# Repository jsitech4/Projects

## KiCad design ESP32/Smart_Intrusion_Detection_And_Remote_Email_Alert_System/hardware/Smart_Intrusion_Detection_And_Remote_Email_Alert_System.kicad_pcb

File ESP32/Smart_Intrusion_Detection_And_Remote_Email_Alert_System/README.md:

# Smart Intrusion Detection and Remote Email Alert System

Standalone ESP32 intrusion detector with local audible alarm, Gmail SMTPS notification, secure local administration, and first-time Wi-Fi provisioning. It reuses the original ESP32 PCB mappings and contains no ESP-NOW or mesh operation.

## Verified PCB mapping

| Function           |  GPIO | Notes                                                        |
| ------------------ | ----: | ------------------------------------------------------------ |
| PIR input          |    26 | HIGH is treated as motion; GPIO26 is RTC-capable.            |
| Buzzer             |    23 | Original firmware energised it HIGH.                         |
| Status LED         |     2 | Active-HIGH patterned status, alert, fault, and network LED. |
| Test button        |    27 | Original active-LOW PCB button, with external bias assumed.  |
| Battery ADC        |    34 | Input-only, original divider scale 1.61.                     |
| Battery gauge LEDs | 16–19 | Active-HIGH 25%, 50%, 75%, and 100% battery-level bars.      |

## Operation

After the configured PIR warm-up, a HIGH PIR signal stable for the motion-confirmation period opens an intrusion event. The buzzer starts immediately, an email is queued on a separate FreeRTOS task, and the current alarm window runs without blocking sensing or the web server. At every alarm boundary, confirmed motion continues the same event and starts another cycle; confirmed clear state ends it.

The device retains only the most recent eight completed intrusion events. This rolling history automatically overwrites the oldest event, keeping persistent storage use predictable and avoiding unnecessary flash growth.

## LED indicators

GPIO2 is the single status LED. Its patterns have priority in this order: intrusion, critical battery, low battery, system fault, Wi-Fi loss, internet loss, PIR warm-up, and configuration mode.

| GPIO2 pattern          | Meaning                                           |
| ---------------------- | ------------------------------------------------- |
| Three rapid flashes    | Intrusion alarm is active.                        |
| Four short flashes     | Critical battery.                                 |
| Two medium flashes     | Low battery.                                      |
| Two fault flashes      | A persistent firmware/system fault.               |
| One long flash         | Wi-Fi is disconnected.                            |
| Two very short flashes | Wi-Fi is connected but the internet check failed. |
| One brief heartbeat    | Powered, healthy, and internet-reachable.         |

GPIO16, GPIO17, GPIO18, and GPIO19 form a cumulative battery bar: one, two, three, or four LEDs represent 1–25%, 26–50%, 51–75%, and 76–100% respectively. The gauge is off when battery monitoring is disabled or the estimated level is empty. Internet reachability is checked with a short TCP probe every 30 seconds; it confirms an external route, not every online service.

## Reliability and automated checks

The ESP32 loop task is protected by a 10-second task watchdog. It is fed only after the complete control loop has run, so a stalled loop resets the device instead of leaving it unresponsive. A reset caused by the watchdog is retained as a fault indication after restart.

The native scenario suite covers battery-gauge boundaries, status-LED priority and pulse timing, and both repeat-alarm paths. Run `tools\run_scenario_tests.bat` to execute it automatically with installed Visual Studio C++ Build Tools. On machines using GCC or MinGW, `platformio test -e native` also works. The production firmware build remains `platformio run -e esp32dev`.

The physical button has two distinct behaviours:

- A short press simulates a PIR intrusion using the complete alarm, log, and notification path.
- Holding it for five seconds opens the configuration access point for two minutes after initial setup. A long press does not simulate an intrusion.

During a configuration window, join the `IntrusionDetector-XXXX` AP. Its generated WPA2 password and `192.168.4.1` address are printed on the serial monitor. On a first boot without saved Wi-Fi, the AP remains active until Wi-Fi is configured.

## Local dashboard and security

Open the device IP address or `http://intrusion-detector.local` after connection. The first visitor must choose an administrator password of at least 12 characters; it is stored as a salted SHA-256 hash. API calls use a time-limited RAM session and CSRF token. Wi-Fi and Gmail passwords are never returned by the configuration API.

This is local HTTP, not HTTPS. Use it only on a trusted LAN and set a strong administrator password. The AP password is emitted only to serial output; treat that serial connection as privileged.

## Gmail

Enter the sender Gmail address, a Google App Password, one to five recipient addresses, and an alert message in the dashboard. Put multiple addresses in the **Recipient email** field separated with commas, semicolons, or line breaks. Addresses are checked, duplicates are removed, and each message uses private SMTP envelope recipients so recipients do not see one another. The firmware connects to `smtp.gmail.com:465` by default and validates TLS with the Google Trust Services root. An accepted SMTP submission is not proof of inbox delivery.

The email subject is generated as `SECURITY ALERT - <device name>`. The alert message is sent exactly as written, followed automatically by the device location, event ID, and NTP-synchronized Nigeria time. The occurrence timestamp is captured when the intrusion begins, so a delayed delivery still reports the original event time.

## Time in Nigeria

The default timezone is `WAT-1` (West Africa Time, UTC+1), which is the POSIX timezone string for Nigeria. After Wi-Fi connects, the ESP32 synchronizes with multiple NTP servers and keeps local event timestamps and email times in WAT. If the connection is lost, it derives time from the last trusted NTP reading and elapsed ESP32 uptime until NTP is available again. The dashboard displays the device's synchronized time; until its first successful NTP sync it reports that the time is unavailable. Keep the timezone set to `WAT-1` for operation in Nigeria.

## Battery-divider calibration

The battery divider scale converts the ESP32 ADC reading on GPIO34 into the actual battery voltage:

```text
battery voltage = ADC-pin voltage × battery divider scale
```

The default scale is `1.61`, taken from the original PCB. To calibrate it, measure the battery with a multimeter (`Vbattery`) and compare it with the voltage shown in the dashboard (`Vshown`). Then save:

```text
new divider scale = current divider scale × (Vbattery ÷ Vshown)
```

For example, if the current scale is `1.61`, the multimeter reads `4.00 V`, and the dashboard reports `3.80 V`, use `1.61 × (4.00 ÷ 3.80) = 1.695`. Recheck the displayed value after saving; calibrate at a normal battery operating voltage.

## Build and flash

Install PlatformIO, then run from this folder:

```powershell
& "$env:USERPROFILE\.platformio\penv\Scripts\platformio.exe" run
& "$env:USERPROFILE\.platformio\penv\Scripts\platformio.exe" run --target upload
& "$env:USERPROFILE\.platformio\penv\Scripts\platformio.exe" device monitor --baud 115200
```

The current target is `esp32dev` (ESP32-WROOM-class, 4 MB flash). Firmware output is `.pio/build/esp32dev/firmware.bin`.

## UI preview

Open [preview_UI/test.html](preview_UI/test.html) in a browser for a static preview of the dashboard. It is illustrative only; it does not connect to an ESP32.

## Commissioning checklist

1. Verify PIR output voltage never exceeds 3.3 V and is LOW while idle.
2. Confirm GPIO23 buzzer polarity and the GPIO2 LED polarity on the physical PCB.
3. Confirm a short button press triggers one alarm cycle and a five-second hold opens AP mode without an alarm.
4. Configure Wi-Fi, Gmail App Password, and up to five recipients; use **Send test email** and confirm delivery to each inbox.
5. Test PIR HIGH for 20, 45, and 65 seconds, then test clear before and at an alarm boundary.
6. Measure sleep/idle power before enabling a battery-saver deep-sleep mode; PIR module, LED, regulator, and ADC divider currents are board-specific and must be measured.

## Security and local configuration

Never commit populated `.env` files, Wi-Fi credentials, passwords, API keys, SMTP credentials, broker tokens, private certificates, or production connection strings. Keep them in an ignored local configuration file or approved secret store, and commit only a redacted `.env.example` when configuration is needed. Replace development access-point credentials before deployment and limit local administration to trusted networks.

# Author

Egbe Raymond

Electrical / Electronic Engineer
Embedded Systems Developer
Full Stack Developer

---

## Engineering asset map and license scope

The editable electrical package is under `hardware/` as a KiCad project,
schematic, and PCB, with project library/3D materials. `documentation/`
contains the schematic and block diagrams, ESP32 reference, and board images;
`production/` contains the BOM, Gerbers, positions, designators, and IPC
netlist. Inspect and modify the source project, then regenerate manufacturing
outputs for a replacement board.

The PlatformIO/Arduino code in `code/` targets `esp32dev` at 115200 baud and
also declares a native test environment. Its modules separate PIR/button
input, buzzer/LED state, Wi-Fi and email delivery, intrusion policy and
controller, event logging/configuration, web administration, battery handling,
and error management. SMTP credentials, Wi-Fi credentials, recipient data, and
event records are deployment secrets or personal data and must not be committed.

The asset-type table below covers original firmware, KiCad files, original images/exports, and project
documentation. ESP32 and sensor material, third-party libraries, mail-service
terms, vendor assets, and trademarks are not relicensed. Consult the
[license scope guide](../../LICENSE-SCOPE.md) and do not treat this prototype
as a certified life-safety or security-response system.

## Licenses

The original JSI Tech material in this mixed engineering project is licensed by
asset type:

| Material | License | Scope |
| --- | --- | --- |
| Software and firmware | [MIT](LICENSE) | Original source code, scripts, configuration examples, tests, and web assets in `code/`. |
| Hardware design | [CERN-OHL-P-2.0](LICENSE-HARDWARE) | Original KiCad/design and manufacturing material in `hardware/` and `production/`. |
| Documentation | [CC BY 4.0](LICENSE-DOCUMENTATION) | Original README text, written documentation, diagrams, photos, and screenshots. |
| External material | [Third-party notices](THIRD-PARTY-NOTICES.md) | Vendor data, third-party libraries/models, dependencies, logos, and other material not created by JSI Tech. |

The [collection licensing guide](../../LICENSE-SCOPE.md) explains the boundary,
required notices, and limitations.

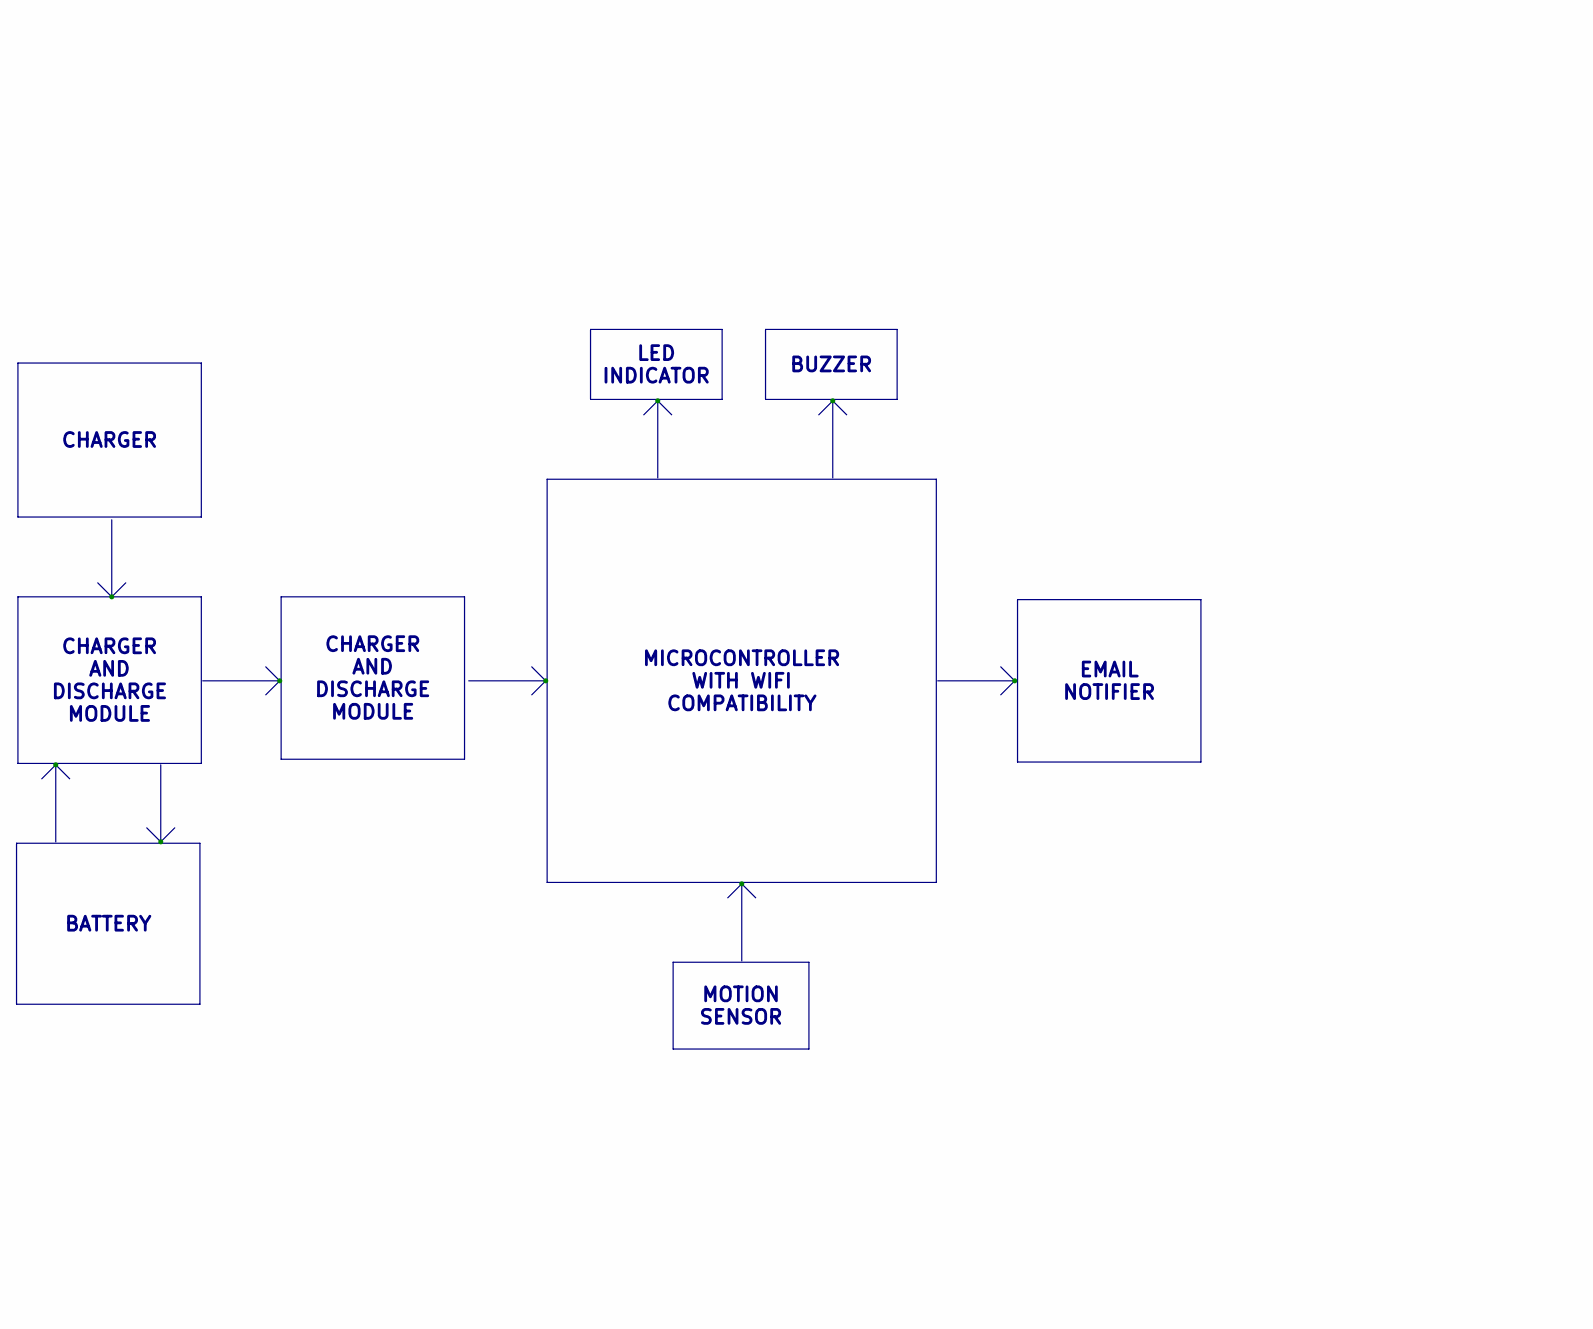
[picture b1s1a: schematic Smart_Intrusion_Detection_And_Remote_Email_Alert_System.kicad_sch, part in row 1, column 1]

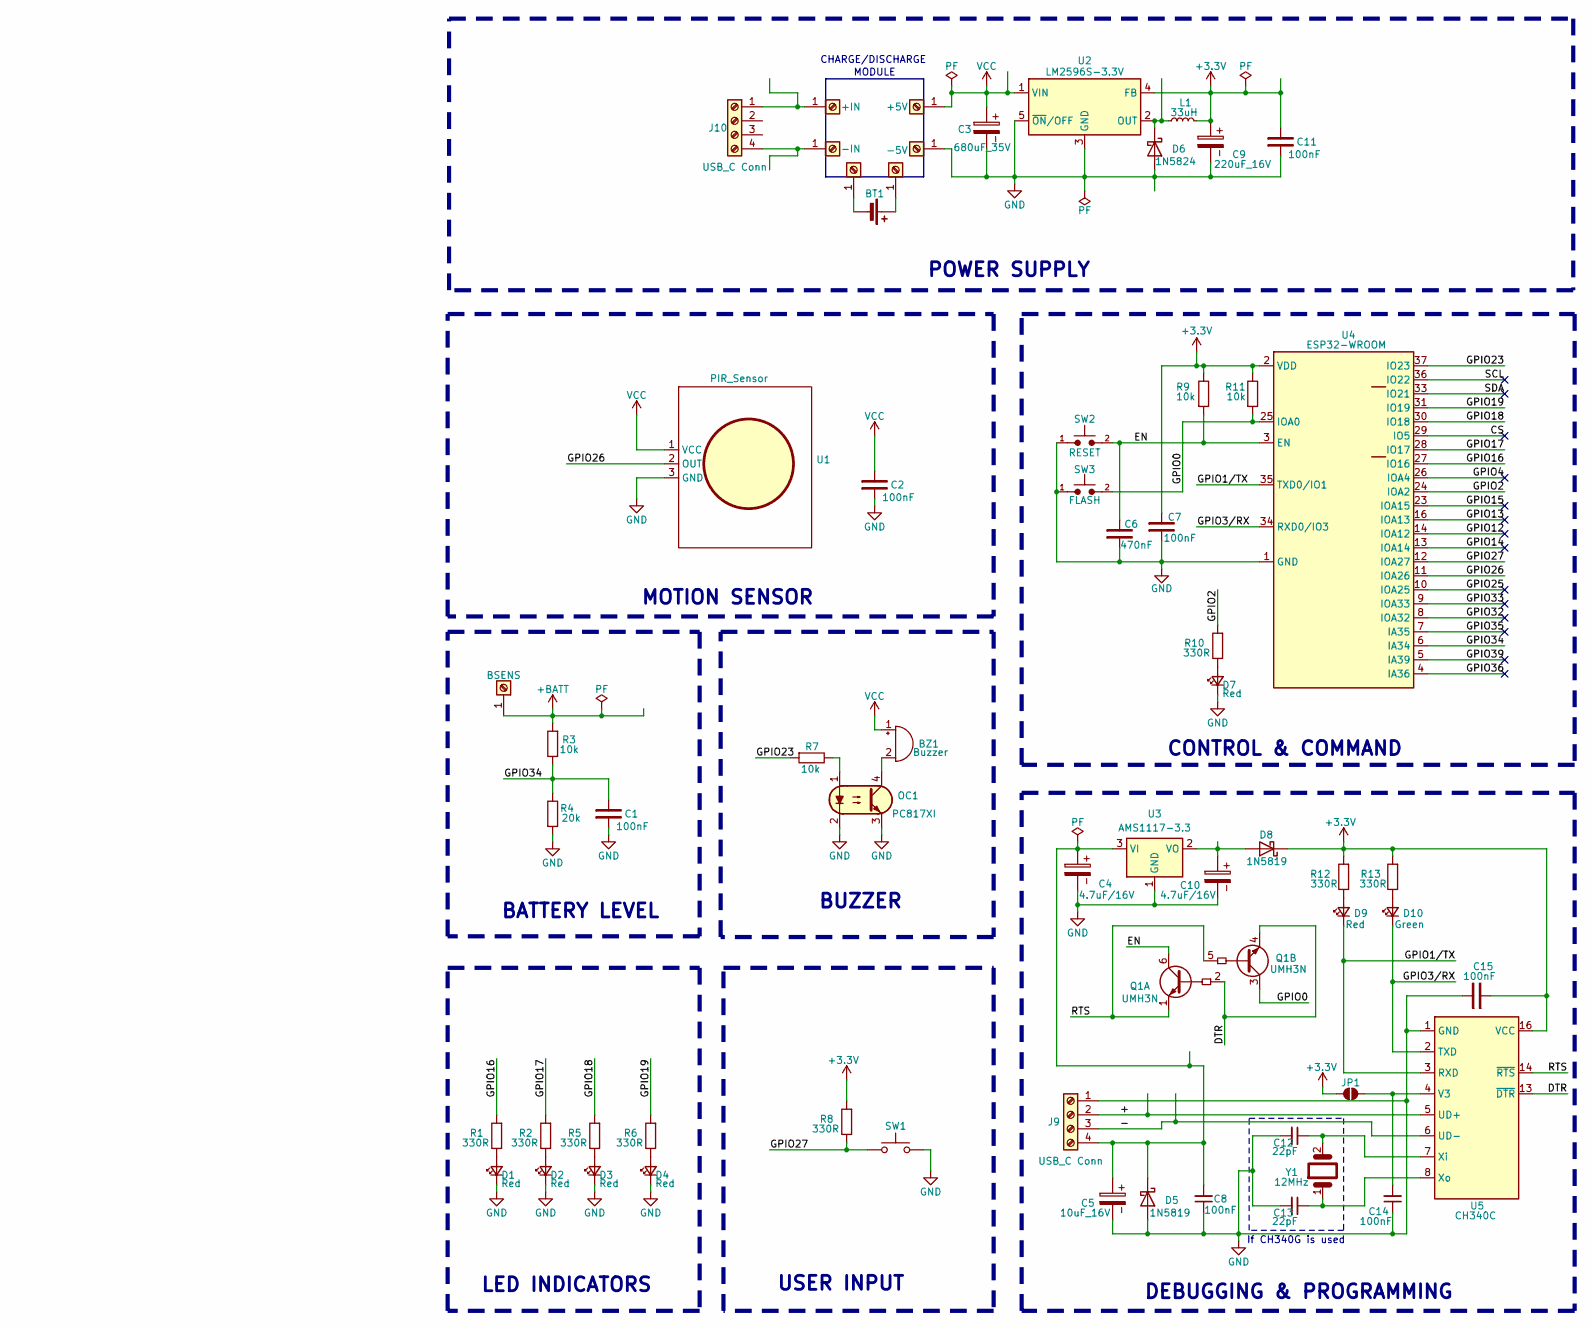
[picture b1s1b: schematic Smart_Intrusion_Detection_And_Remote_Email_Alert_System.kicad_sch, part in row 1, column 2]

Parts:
BT1: Battery_Cell
BZ1: Buzzer; Buzzer_15x7.5RM7.6
C1, C2, C7, C8, C11, C14, C15: 100nF; C_0805_2012Metric_Pad1.18x1.45mm_HandSolder
C3: 680uF_35V; CP_Elec_10x12.5
C4, C10: 4.7uF/16V; CP_EIA-3528-21_Kemet-B_HandSolder
C5: 10uF_16V; CP_Radial_D5.0mm_P2.00mm
C6: 470nF; C_0805_2012Metric_Pad1.18x1.45mm_HandSolder
C9: 220uF_16V; CP_Elec_6.3x7.7
C12, C13: 22pF; C_0805_2012Metric_Pad1.18x1.45mm_HandSolder
D1, D2, D3, D4, D7, D9: Red; LED_D3.0mm
D5, D8: 1N5819; D_SMA
D6: 1N5824; D_SMA
D10: Green; LED_D3.0mm
J1: BSENS; SolderWire-0.1sqmm_1x01_D0.4mm_OD1mm
J3: +IN; TestPoint_Keystone_5015_Micro_Mini
J4: -IN; TestPoint_Keystone_5015_Micro_Mini
J5: -BATT
J6: +BATT
J7: +5V; TestPoint_Keystone_5015_Micro_Mini
J8: -5V; TestPoint_Keystone_5015_Micro_Mini
J9, J10: USB_C Conn; PinHeader_1x04_P2.54mm_Vertical
JP1: SolderJumper-2_P1.3mm_Open_Pad1.0x1.5mm
L1: 33uH; L_12x12mm_H6mm
OC1: PC817XI; SMDIP-4_W9.53mm
Q1: UMH3N; SOT-363_SC-70-6
R1, R2, R5, R6, R8, R10, R12, R13: 330R; R_0805_2012Metric
R3, R7, R9, R11: 10k; R_0805_2012Metric
R4: 20k; R_0805_2012Metric
SW1: SW_Push; PinHeader_1x02_P2.54mm_Vertical
SW2: RESET; SW_SPST_CK_KXT3
SW3: FLASH; SW_SPST_CK_KXT3
U1: PIR_Sensor; PinHeader_1x03_P2.54mm_Vertical
U2: LM2596S-3.3V; TO-263-5_TabPin6
U3: AMS1117-3.3; SOT-223-3_TabPin2
U4: ESP32-WROOM; ESP32-WROOM-32U
U5: CH340C; SOIC-16_3.9x9.9mm_P1.27mm
Y1: 12MHz; Crystal_HC49-4H_Vertical

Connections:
+3.3V: C7.2, C9.1, C11.2, C15.1, D8.1 (K), JP1.2 (B), L1.2, R8.1, R9.2, R11.2, R12.1, R13.1, U2.4 (FB), U4.2 (VDD), U5.16 (VCC)
+BATT: J1.1, R3.1
/+: J9.2, U5.5 (UD+)
/-: J9.3, U5.6 (UD-)
/CS: U4.29 (IO5)
/DTR: Q1.2 (B1), Q1.4 (E2), U5.13 (~DTR)
/EN: C6.2, Q1.6 (C1), R9.1, SW2.2, U4.3 (EN)
/GPIO0: Q1.3 (C2), R11.1, SW3.2, U4.25 (IOA0)
/GPIO1/TX: D9.1 (K), U4.35 (TXD0/IO1), U5.3 (RXD)
/GPIO2: R10.1, U4.24 (IOA2)
/GPIO3/RX: D10.1 (K), U4.34 (RXD0/IO3), U5.2 (TXD)
/GPIO4: U4.26 (IOA4)
/GPIO12: U4.14 (IOA12)
/GPIO13: U4.16 (IOA13)
/GPIO14: U4.13 (IOA14)
/GPIO15: U4.23 (IOA15)
/GPIO16: R1.1, U4.27 (IO16)
/GPIO17: R2.1, U4.28 (IO17)
/GPIO18: R5.1, U4.30 (IO18)
/GPIO19: R6.1, U4.31 (IO19)
/GPIO23: R7.1, U4.37 (IO23)
/GPIO25: U4.10 (IOA25)
/GPIO26: U1.2 (OUT), U4.11 (IOA26)
/GPIO27: R8.2, SW1.1, U4.12 (IOA27)
/GPIO32: U4.8 (IOA32)
/GPIO33: U4.9 (IOA33)
/GPIO34: C1.2, R3.2, R4.2, U4.6 (IA34)
/GPIO35: U4.7 (IA35)
/GPIO36: U4.4 (IA36)
/GPIO39: U4.5 (IA39)
/RTS: Q1.1 (E1), Q1.5 (B2), U5.14 (~RTS)
/SCL: U4.36 (IO22)
/SDA: U4.33 (IO21)
GND: C1.1, C2.1, C3.2, C4.2, C5.2, C6.1, C7.1, C8.1, C9.2, C10.2, C11.1, C12.2, C13.2, C14.1, C15.2, D1.1 (K), D2.1 (K), D3.1 (K), D4.1 (K), D5.2 (A), D6.2 (A), D7.1 (K), J8.1, J9.1, OC1.2, OC1.3, R4.1, SW1.2, SW2.1, SW3.1, U1.3 (GND), U2.3 (GND), U2.5 (~ON/OFF), U2.6 (GND), U3.1 (GND), U4.1 (GND), U4.15 (GND), U4.38 (GND), U4.39 (GND), U5.1 (GND)
unnamed: BT1.1 (+), J6.1
unnamed: BT1.2 (-), J5.1
unnamed: BZ1.2 (-), OC1.4
unnamed: D1.2 (A), R1.2
unnamed: D2.2 (A), R2.2
unnamed: D3.2 (A), R5.2
unnamed: D4.2 (A), R6.2
unnamed: C4.1, C5.1, C8.2, D5.1 (K), J9.4, U3.3 (VI)
unnamed: D6.1 (K), L1.1, U2.2 (OUT)
unnamed: D7.2 (A), R10.2
unnamed: C10.1, D8.2 (A), U3.2 (VO)
unnamed: D9.2 (A), R12.2
unnamed: D10.2 (A), R13.2
unnamed: J3.1, J10.1
unnamed: J4.1, J10.4
unnamed: C14.2, JP1.1 (A), U5.4 (V3)
unnamed: OC1.1, R7.2
unnamed: C12.1, U5.7 (Xi), Y1.2
unnamed: C13.1, U5.8 (Xo), Y1.1
VCC: BZ1.1 (+), C2.2, C3.1, J7.1, U1.1 (VCC), U2.1 (VIN)

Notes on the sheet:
MOTION SENSOR
MODULE
BUZZER
POWER SUPPLY
CHARGE/DISCHARGE
If CH340G is used
BATTERY LEVEL
LED INDICATORS
DEBUGGING & PROGRAMMING
CONTROL & COMMAND
USER INPUT
MOTION SENSOR
LED INDICATOR
CHARGER
EMAIL NOTIFIER
BATTERY
MICROCONTROLLER WITH WIFI COMPATIBILITY
CHARGER AND DISCHARGE MODULE

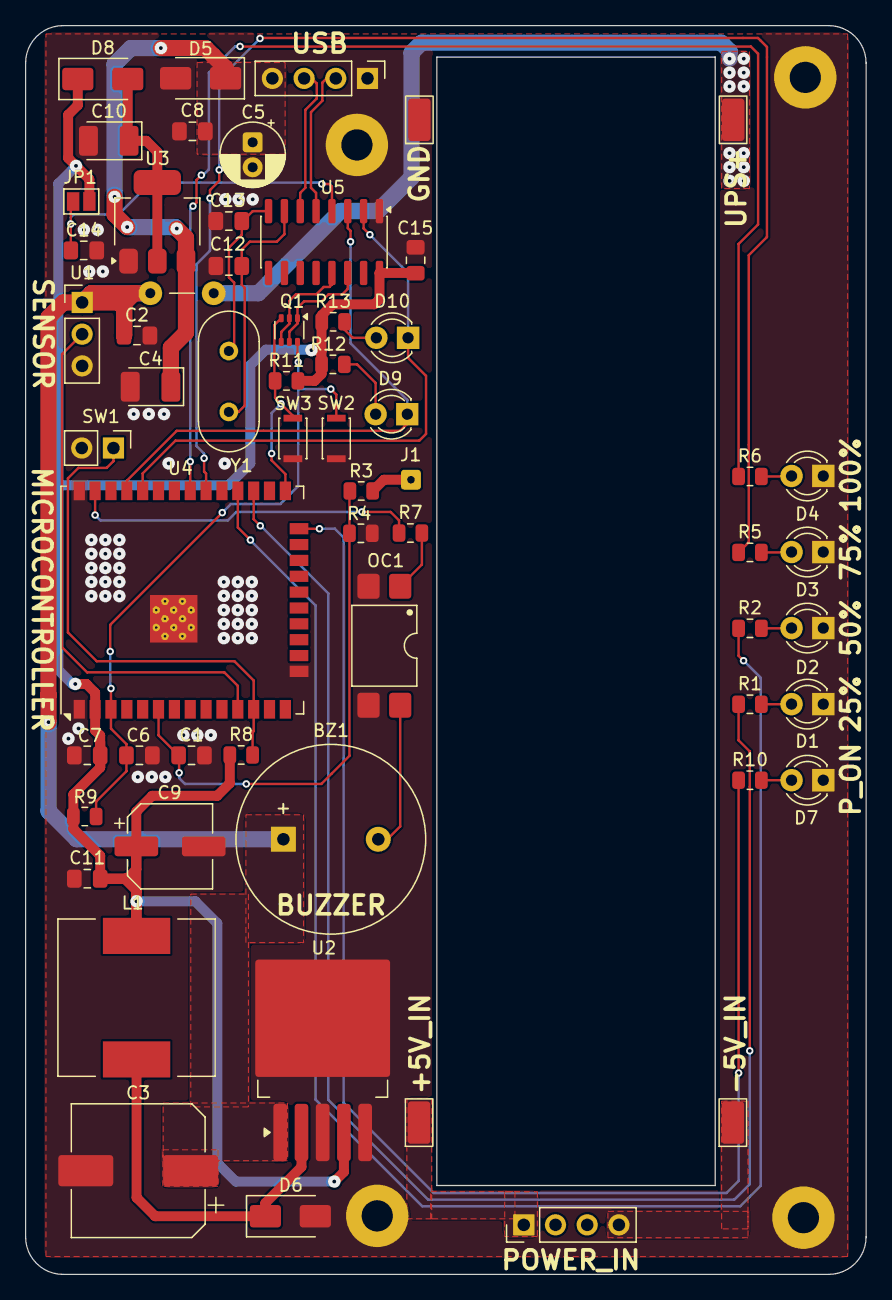
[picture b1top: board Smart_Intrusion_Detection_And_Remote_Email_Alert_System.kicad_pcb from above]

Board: 2 copper layers, 67.3 x 100.0 mm, 59 parts (0 on the bottom side), 38 nets.

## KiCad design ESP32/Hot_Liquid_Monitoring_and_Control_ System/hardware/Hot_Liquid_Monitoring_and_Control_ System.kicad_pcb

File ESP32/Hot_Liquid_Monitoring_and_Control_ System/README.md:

# Hot Liquid Monitoring and Control System

ESP32-S3 firmware and KiCad hardware for monitoring liquid temperature and vessel level, presenting live status on a local dashboard/LCD, recording events, and driving a protected relay output according to configurable level and temperature rules.

## What it does

- Measures temperature through a MAX31865 RTD interface and liquid distance/level through an ultrasonic sensor.
- Converts distance to a configurable percentage level and classifies low/normal/full tank states.
- Classifies temperature against configurable low/high limits.
- Combines independent automatic demands with a persistent manual relay request; the effective relay request is `manual OR automatic`.
- Provides latching modes for tank and temperature events, a buzzer/LED indication path, local web dashboard, LCD output, internal flash settings/event storage, sleep/wake service, and reset handling.

## Hardware mapping

| Function | ESP32-S3 GPIO | Notes |
| --- | ---: | --- |
| I2C SDA / SCL | 8 / 9 | LCD and I2C peripherals. |
| ZMCT103C ADC | 1 | Defined on the PCB pin map; verify use before enabling. |
| ADXL345 interrupt | 10 | Defined on the PCB pin map; not part of the primary control loop. |
| DS18B20 data | 4 | Defined on the PCB pin map. |
| SPI CS / MOSI / SCK / MISO | 5 / 11 / 12 / 13 | Reserved interface pins. |
| Ultrasonic trigger / echo | 17 / 18 | Level sensor; condition echo voltage for 3.3 V logic. |
| Buzzer | 14 | Active level must match the installed driver. |
| Relay | 21 | Verify relay polarity and load isolation before use. |
| Status LED | 48 | Local state indication. |
| UART0 TX / RX | 43 / 44 | Serial/programming interface. |
| Boot | 0 | Do not load in a way that prevents boot. |

The deployed hardware and source of truth are in `hardware/` and `code/lib/Pins/Pins.cpp`. Review the KiCad schematic before connecting sensors or mains-powered equipment.

## Operating model

At startup the firmware restores a validated saved configuration or retains safe defaults. Each loop updates the RTD and ultrasonic sensors, evaluates `device_manager`, applies the relay request, updates buzzer/LED/LCD/storage/web services, and yields. A latched automatic threshold event cannot be cleared merely by changing settings: `clearFault()` rechecks valid, current inputs and clears only when all enabled threshold conditions have recovered. Manual relay requests remain separate from faults.

The local web UI exposes live state, configuration, event records, manual relay control, and guarded fault clearing. Treat browser controls as an operator interface—not as a substitute for thermal cut-outs, pressure relief, contactors, or independent safety interlocks.

## Build, upload, and test

Prerequisites: PlatformIO Core, an ESP32-S3 DevKitC-1, and the components stated in `platformio.ini` (LiquidCrystal_I2C, Adafruit ADXL345, and Adafruit MAX31865).

```powershell
cd code
pio run -e esp32-s3
pio device list
pio run -e esp32-s3 -t upload
pio device monitor -b 115200
```

Run the host fault tests from `code` using the project’s test configuration. Before energizing a live actuator, test with the relay load disconnected, verify the output polarity, calibrate full/low vessel distances, validate temperature limits with a reference thermometer, and confirm the relay remains de-energized on reset and sensor error.

## Configuration and usage

1. Wire only isolated, low-voltage sensor signals. The ultrasonic echo input must be reduced to 3.3 V logic.
2. Flash the firmware and connect to the device’s local access point/dashboard as reported by the firmware.
3. Set full and low distances, level thresholds, temperature limits, and the intended latch modes.
4. Verify level conversion with known vessel levels; verify the RTD reading against a trusted thermometer.
5. Test automatic demand, manual demand, latch clearing, buzzer/LED, dashboard, and persistence with no hazardous load attached.
6. Connect the final relay through a correctly rated, isolated driver and independently verify fail-safe behavior.

## Project layout

| Path | Purpose |
| --- | --- |
| `hardware/` | KiCad project, symbols, footprints, 3D models, and PCB design. |
| `code/src/` | Firmware entry point and initialization order. |
| `code/lib/Control/` | Control state, fault logic, sleep/reset, and device manager. |
| `code/lib/Sensors/` | RTD and ultrasonic acquisition. |
| `code/lib/Actuators/`, `Display/`, `Communication/` | Relay, buzzer, UI, and local server. |
| `code/lib/Storage/` | Persistent settings and event history. |
| `production/` | BOM, fabrication, and Gerber deliverables. |

## Security and secrets

Do not place Wi-Fi credentials, local dashboard passwords, cloud/API tokens, or private certificates in committed source. Store them in a local `.env`/ignored configuration file and inject them during the build or provisioning process; provide only a redacted `.env.example` when adding configuration. Change any development access-point password before deployment, restrict the configuration network to trusted users, and do not expose an unauthenticated control UI to the internet.

## Safety

Hot liquid, heaters, pumps, and mains equipment can cause burns, fire, electrocution, or pressure hazards. This project is not a certified safety controller. Use a qualified electrician, fused and grounded hardware, rated contactors/SSR drivers, a mechanical thermal cut-out, independent over-temperature and dry-run protection, emergency isolation, and local regulatory requirements. Never rely on firmware alone to protect people or equipment.

# Author

Egbe Raymond

Electrical / Electronic Engineer
Embedded Systems Developer
Full Stack Developer

---

## Engineering asset map and license scope

The KiCad schematic, PCB, and project source are in `hardware/`; its symbols,
footprints, 3D assets, source imagery, block/schematic PDFs, and ESP32-S3
reference are kept with `hardware/` and `documentation/`. `production/`
contains Gerbers, BOM, positions, designators, and IPC netlist for fabrication.
Review the schematic and regenerate these exports after any electrical change.

`code/` is an Arduino PlatformIO firmware project for `esp32-s3-devkitc-1` at
115200 baud. Modules isolate temperature and ultrasonic sensing, relay and
buzzer actuation, LCD/LED indication, storage, local web service, device
management, error handling, reset, and sleep/wake behavior. The firmware is a
prototype control implementation; set points, sensor calibration, relay
polarity, fail-safe state, and over-temperature protection must be verified on
the actual vessel and load.

The asset-type table below applies to original project firmware, KiCad sources, original library
assets, fabrication exports, images, and documentation. Datasheets, vendor
models, external libraries, components, and tool output governed by another
notice are excluded from that grant. See the [license scope guide](../../LICENSE-SCOPE.md),
especially its hardware and safety section.

## Licenses

The original JSI Tech material in this mixed engineering project is licensed by
asset type:

| Material | License | Scope |
| --- | --- | --- |
| Software and firmware | [MIT](LICENSE) | Original source code, scripts, configuration examples, tests, and web assets in `code/`. |
| Hardware design | [CERN-OHL-P-2.0](LICENSE-HARDWARE) | Original KiCad/design and manufacturing material in `hardware/` and `production/`. |
| Documentation | [CC BY 4.0](LICENSE-DOCUMENTATION) | Original README text, written documentation, diagrams, photos, and screenshots. |
| External material | [Third-party notices](THIRD-PARTY-NOTICES.md) | Vendor data, third-party libraries/models, dependencies, logos, and other material not created by JSI Tech. |

The [collection licensing guide](../../LICENSE-SCOPE.md) explains the boundary,
required notices, and limitations.

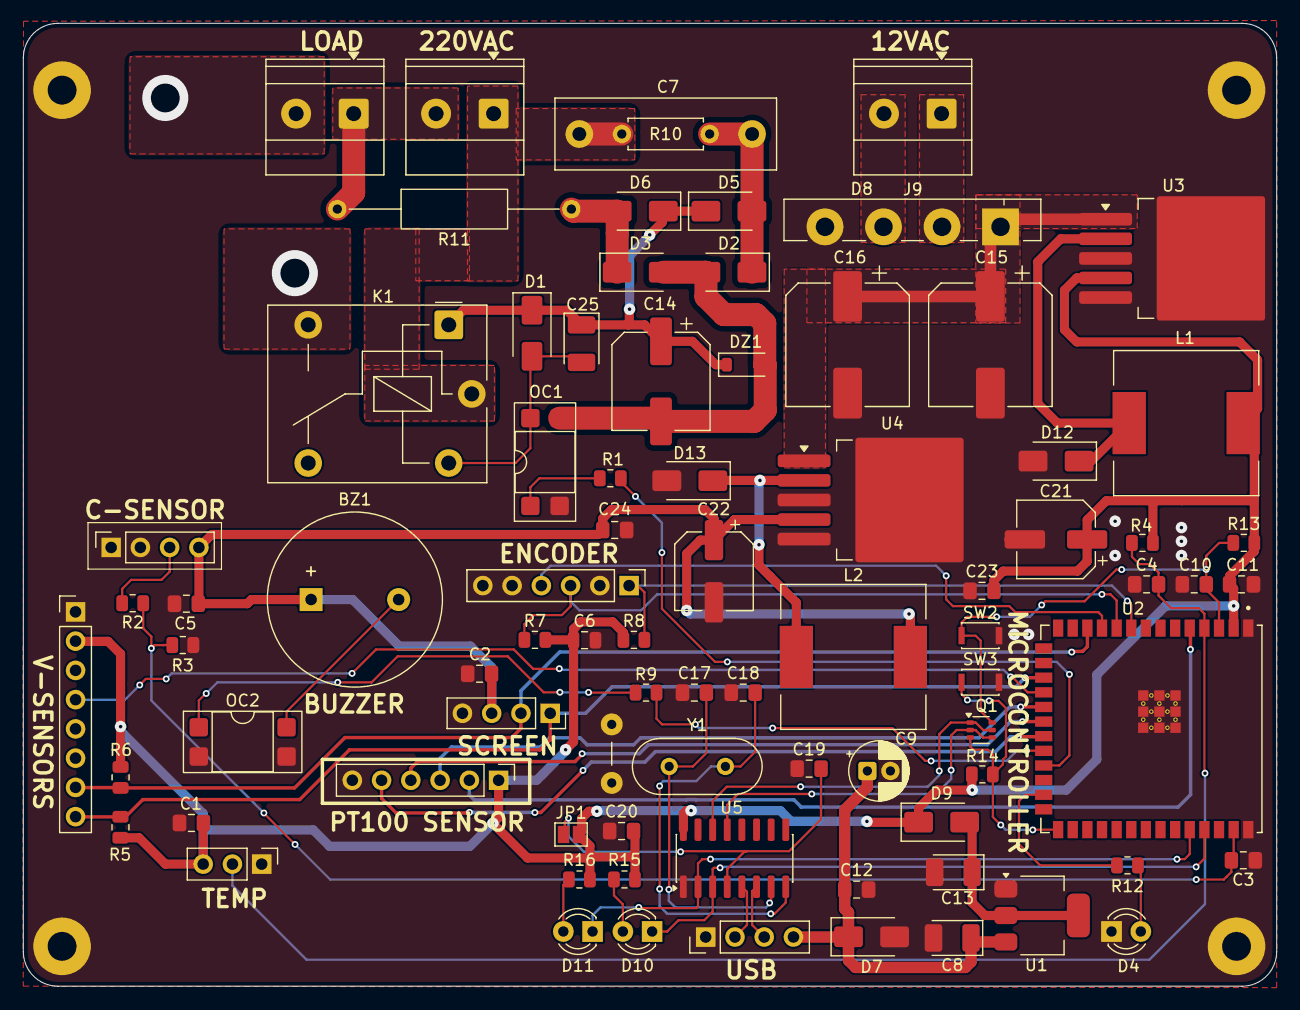
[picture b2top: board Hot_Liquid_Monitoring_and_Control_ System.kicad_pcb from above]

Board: 2 copper layers, 108.8 x 83.6 mm, 81 parts (0 on the bottom side), 51 nets.

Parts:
BZ1: Buzzer; Buzzer_15x7.5RM7.6
C1, C2, C3, C4, C5, C11, C12, C19, C20, C23, C24: 100nF; C_0805_2012Metric_Pad1.18x1.45mm_HandSolder
C6: 104; C_0805_2012Metric
C7: 145J400V; C_Rect_L19.0mm_W6.0mm_P15.00mm_MKS4
C8, C13, C25: 4.7uF/16V; CP_EIA-3528-21_Kemet-B_HandSolder
C9: 10uF_16V; CP_Radial_D5.0mm_P2.00mm
C10: 470nF; C_0805_2012Metric_Pad1.18x1.45mm_HandSolder
C14: 470uF/25V; CP_Elec_8x11.9
C15, C16: 680uF_35V; CP_Elec_10x12.5
C17, C18: 22pF; C_0805_2012Metric_Pad1.18x1.45mm_HandSolder
C21, C22: 220uF_16V; CP_Elec_6.3x7.7
D1: 1N4007; D_SMA
D2, D3, D5, D6: SM4001; D_SMA
D4, D10: Red; LED_D3.0mm
D7, D9: 1N5819; D_SMA
D8: GBU8M; Diode_Bridge_Vishay_GBU
D11: Green; LED_D3.0mm
D12, D13: 1N5824; D_SMA
DZ1: CMZ12; D_SOD-123
J1: DS18B20; PinHeader_1x03_P2.54mm_Vertical
J2: CURRENT SENSOR; PinSocket_1x04_P2.54mm_Vertical
J3: OLED SCREEN; PinSocket_1x04_P2.54mm_Vertical
J4: LOAD; TerminalBlock_Phoenix_MKDS-1,5-2_1x02_P5.00mm_Horizontal
J5: 220VAC; TerminalBlock_Phoenix_MKDS-1,5-2_1x02_P5.00mm_Horizontal
J6: MPU6050; PinHeader_1x08_P2.54mm_Vertical
J7: SD MODULE; PinHeader_1x06_P2.54mm_Vertical
J8: USB_C Conn; PinHeader_1x04_P2.54mm_Vertical
J9: 12VAC; TerminalBlock_Phoenix_MKDS-1,5-2_1x02_P5.00mm_Horizontal
JP1: SolderJumper-2_P1.3mm_Open_Pad1.0x1.5mm
K1: FINDER-36.11; Relay_SPDT_Finder_36.11
L1, L2: 33uH; L_12x12mm_H6mm
OC1, OC2: PC817XI; DIP-4_W7.62mm_SMDSocket_SmallPads
Q1: UMH3N; SOT-363_SC-70-6
R1, R4, R5, R6, R7, R8, R9, R13, R14: 10k; R_0805_2012Metric
R2: 1k; R_0805_2012Metric
R3: 2k; R_0805_2012Metric
R10: 1M; R_Axial_DIN0207_L6.3mm_D2.5mm_P7.62mm_Horizontal
R11: 330R/2W; R_Axial_DIN0309_L9.0mm_D3.2mm_P20.32mm_Horizontal
R12, R15, R16: 330R; R_0805_2012Metric
SW1: RotaryEncoder; PinHeader_1x06_P2.54mm_Vertical
SW2: RESET; SW_SPST_CK_KXT3
SW3: FLASH; SW_SPST_CK_KXT3
U1: AMS1117-3.3; SOT-223-3_TabPin2
U2: ESP32-S3-WROOM-1U-N16R8
U3: LM2596S-3.3V; TO-263-5_TabPin6
U4: LM2596S-5V; TO-263-5_TabPin6
U5: CH340C; SOIC-16_3.9x9.9mm_P1.27mm
Y1: 12MHz; Crystal_HC49-4H_Vertical

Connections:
+3.3V: C1.2, C6.1, C11.2, C20.1, C21.1, C23.2, D9.1 (K), J1.3, J6.2, J7.1, JP1.2 (B), L1.2, R4.1, R5.1, R6.1, R7.2, R8.1, R13.2, R14.2, R15.1, R16.1, U2.2 (3V3), U3.4 (FB), U5.16 (VCC)
+5V: BZ1.1 (+), C2.1, C5.2, C22.1, C24.2, J2.4, J3.3, L2.2, U4.4 (FB)
/+: J8.2, U5.5 (UD+)
/-: J8.3, U5.6 (UD-)
/CS: J7.2, U2.5 (IO5)
/DTR: Q1.2 (B1), Q1.4 (E2), U5.13 (~DTR)
/EN: C10.2, Q1.6 (C1), R13.1, SW2.2, U2.3 (EN)
/GPIO0: Q1.3 (C2), R14.1, SW3.2, U2.27 (IO0)
/GPIO1: C3.2, R2.2, R3.1, U2.39 (IO1)
/GPIO4: C4.2, J1.2, R4.2, U2.4 (IO4)
/GPIO14: R9.1, U2.22 (IO14)
/GPIO16: R8.2, SW1.1 (A), U2.9 (IO16)
/GPIO17: R7.1, SW1.3 (B), U2.10 (IO17)
/GPIO18: SW1.4 (S1), U2.11 (IO18)
/GPIO21: R1.1, U2.23 (IO21)
/GPIO43/TX: D10.1 (K), U2.37 (TXD0), U5.3 (RXD)
/GPIO44/RX: D11.1 (K), U2.36 (RXD0), U5.2 (TXD)
/GPIO48: R12.1, U2.25 (IO48)
/INT1: J6.4, U2.18 (IO10)
/LIVE: C7.2, J5.1, K1.11, R10.2
/MISO: J7.5, U2.21 (IO13)
/MOSI: J7.3, U2.19 (IO11)
/NEUTRAL: J4.1, J5.2, R11.1
/RTS: Q1.1 (E1), Q1.5 (B2), U5.14 (~RTS)
/SCK: J7.4, U2.20 (IO12)
/SCL: J3.1, J6.8, R5.2, U2.17 (IO9)
/SDA: J3.2, J6.7, R6.2, U2.12 (IO8)
/VCC1: C15.1, C16.1, D8.1 (+), U3.1 (VIN), U4.1 (VIN)
GND: C1.1, C2.2, C3.1, C4.1, C5.1, C6.2, C8.2, C9.2, C10.1, C11.1, C12.1, C13.2, C15.2, C16.2, C17.2, C18.2, C19.1, C20.2, C21.2, C22.2, C23.1, C24.1, D4.1 (K), D7.2 (A), D8.4 (-), D12.2 (A), D13.2 (A), J1.1, J2.1, J2.2, J3.4, J6.1, J7.6, J8.1, OC1.2, OC2.2, OC2.3, R3.2, SW1.2 (C), SW1.5 (S2), SW1.6 (MP), SW2.1, SW3.1, U1.1 (GND), U2.1 (GND), U2.40 (GND), U2.41 (GND), U3.3 (GND), U3.5 (~ON/OFF), U3.6 (GND), U4.3 (GND), U4.5 (~ON/OFF), U4.6 (GND), U5.1 (GND)
GNDA: C14.2, D2.2 (A), D3.2 (A), DZ1.2 (A), OC1.3
unnamed: BZ1.2 (-), OC2.4
unnamed: C25.2, D1.2 (A), K1.A2, OC1.4
unnamed: C7.1, D2.1 (K), D5.2 (A), R10.1
unnamed: D3.1 (K), D6.2 (A), R11.2
unnamed: D4.2 (A), R12.2
unnamed: C8.1, C9.1, C12.2, D7.1 (K), J8.4, U1.3 (VI)
unnamed: C13.1, D9.2 (A), U1.2 (VO)
unnamed: D10.2 (A), R15.2
unnamed: D11.2 (A), R16.2
unnamed: D12.1 (K), L1.1, U3.2 (OUT)
unnamed: D13.1 (K), L2.1, U4.2 (OUT)
unnamed: J2.3, R2.1
unnamed: J4.2, K1.14
unnamed: D8.2, J9.1
unnamed: D8.3, J9.2
unnamed: C19.2, JP1.1 (A), U5.4 (V3)
unnamed: OC1.1, R1.2
unnamed: OC2.1, R9.2
unnamed: C17.1, U5.7 (Xi), Y1.2
unnamed: C18.1, U5.8 (Xo), Y1.1
VCC2: C14.1, C25.1, D1.1 (K), D5.1 (K), D6.1 (K), DZ1.1 (K), K1.A1

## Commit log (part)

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2025-11-19 update from work
2025-11-21 PCB layer ready for printing
